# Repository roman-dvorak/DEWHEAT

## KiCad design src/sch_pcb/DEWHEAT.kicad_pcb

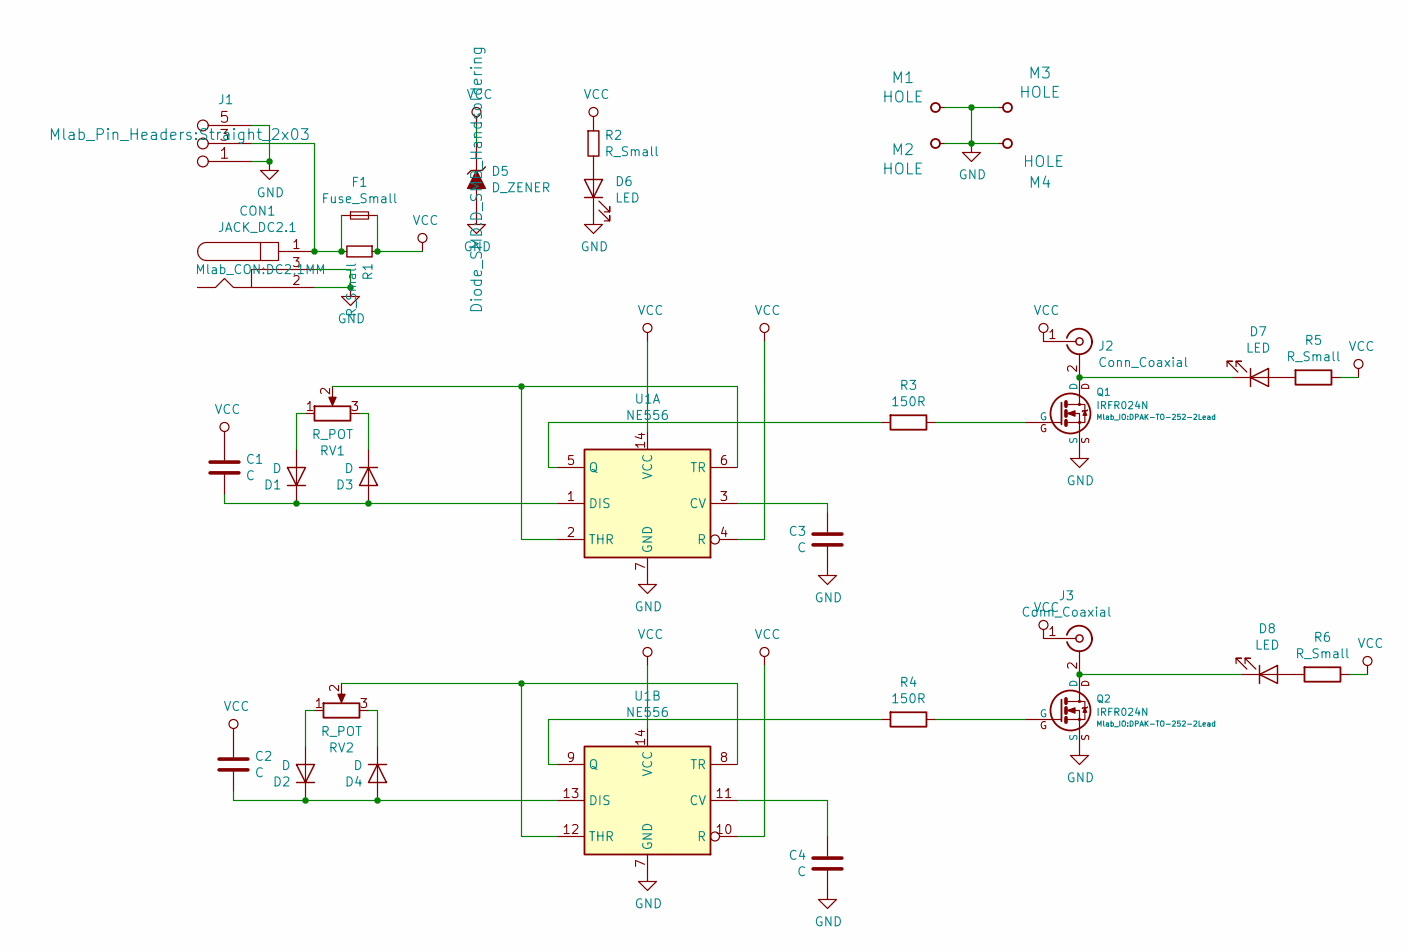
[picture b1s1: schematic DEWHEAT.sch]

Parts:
C1, C2, C3, C4: C; SMD-0805
CON1: JACK_DC2.1; DC2,1MM
D1, D2, D3, D4: D; SMD-0805
D5: D_ZENER; D_SMB_Handsoldering
D6, D7, D8: LED; LED_1206
F1: Fuse_Small; Drzak_2410
J1: JUMP_3X2; Straight_2x03
J2, J3: Conn_Coaxial; Straight_1x02
M1, M2, M3, M4: HOLE; MountingHole_3mm
Q1, Q2: IRFR024N; DPAK-TO-252-2Lead
R1, R2, R5, R6: R_Small; SMD-0805
R3, R4: 150R; SMD-0805
RV1, RV2: R_POT; Straight_1x03
U1: NE556; SOIC-14_3.9x8.7mm_P1.27mm

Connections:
GND: C3.2, C4.2, CON1.2, CON1.3, D5.2 (A), D6.1 (K), J1.1 (2), J1.2, J1.5 (6), J1.6, M1.1, M2.1, M3.1, M4.1, Q1.S, Q2.S, U1.7 (GND)
unnamed: C1.2, D1.1 (K), D3.2 (A), U1.1 (DIS)
unnamed: C2.2, D2.1 (K), D4.2 (A), U1.13 (DIS)
unnamed: C3.1, U1.3 (CV)
unnamed: C4.1, U1.11 (CV)
unnamed: CON1.1, F1.1, J1.3 (4), J1.4, R1.2
unnamed: D1.2 (A), RV1.1
unnamed: D2.2 (A), RV2.1
unnamed: D3.1 (K), RV1.3
unnamed: D4.1 (K), RV2.3
unnamed: D6.2 (A), R2.2
unnamed: D7.1 (K), J2.2 (Ext), Q1.D
unnamed: D7.2 (A), R5.2
unnamed: D8.1 (K), J3.2 (Ext), Q2.D
unnamed: D8.2 (A), R6.2
unnamed: Q1.G, R3.1
unnamed: Q2.G, R4.1
unnamed: R3.2, U1.5 (Q)
unnamed: R4.2, U1.9 (Q)
unnamed: RV1.2, U1.2 (THR), U1.6 (TR)
unnamed: RV2.2, U1.8 (TR), U1.12 (THR)
VCC: C1.1, C2.1, D5.1 (K), F1.2, J2.1 (In), J3.1 (In), R1.1, R2.1, R5.1, R6.1, U1.4 (R), U1.10 (R), U1.14 (VCC)

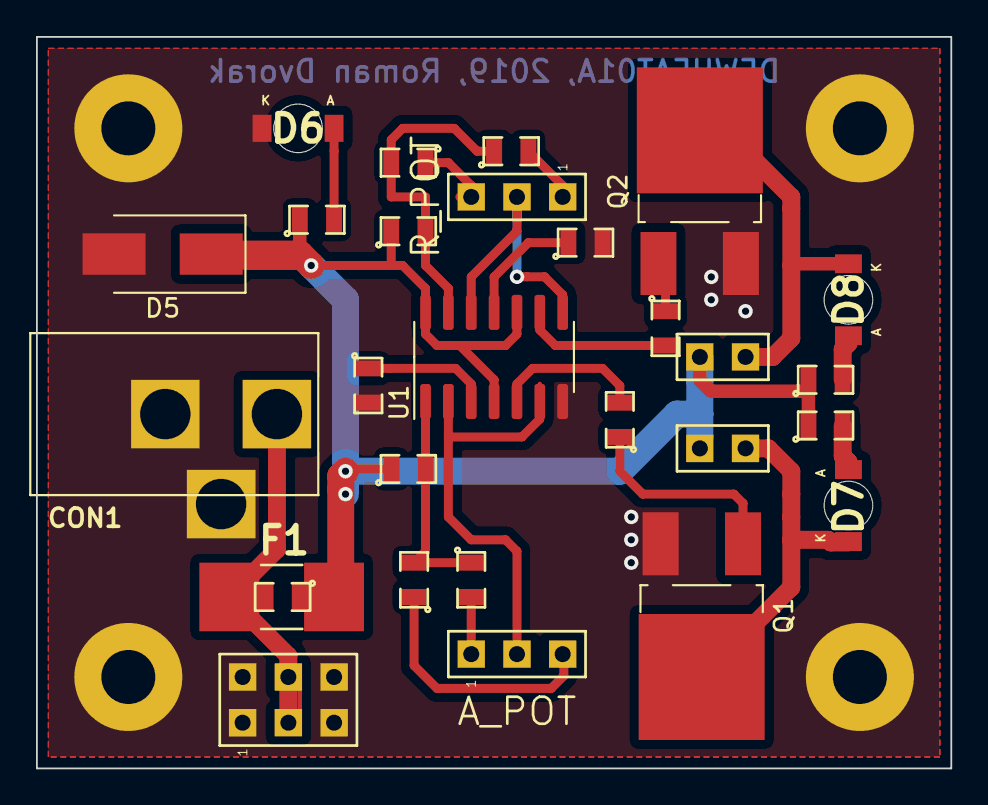
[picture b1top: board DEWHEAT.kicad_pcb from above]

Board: 2 copper layers, 50.8 x 40.6 mm, 32 parts (0 on the bottom side), 22 nets.
